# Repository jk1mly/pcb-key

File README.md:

アルプスのSKRHAAE010を使って、スイッチの状態により異なる電圧が出るようにして、A/Dして状態を読み込む基板

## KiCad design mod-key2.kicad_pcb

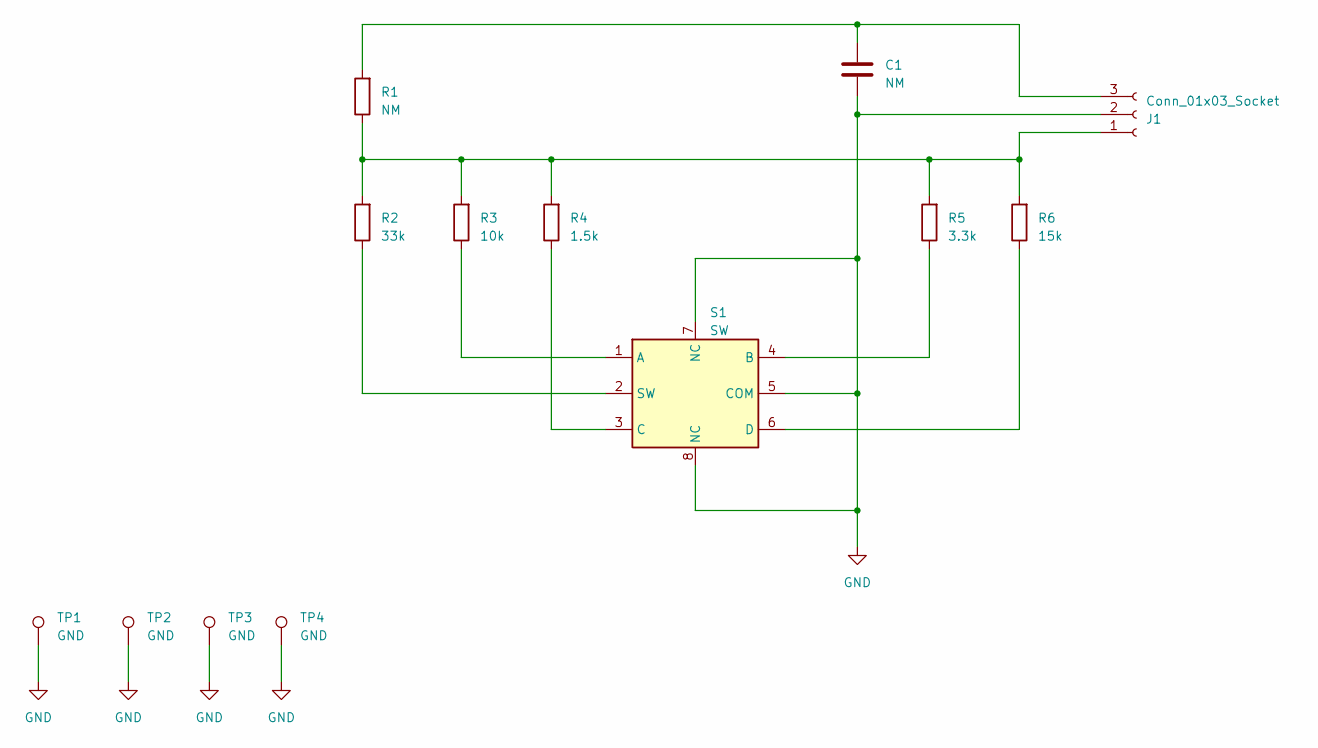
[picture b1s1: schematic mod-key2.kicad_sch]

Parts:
C1: NM; C_Disc_D3.4mm_W2.1mm_P2.50mm
J1: Conn_01x03_Socket; PinSocket_1x03_P2.54mm_Vertical
R1: NM; R_Axial_DIN0207_L6.3mm_D2.5mm_P7.62mm_Horizontal
R2: 33k; R_Axial_DIN0207_L6.3mm_D2.5mm_P7.62mm_Horizontal
R3: 10k; R_Axial_DIN0207_L6.3mm_D2.5mm_P7.62mm_Horizontal
R4: 1.5k; R_Axial_DIN0207_L6.3mm_D2.5mm_P7.62mm_Horizontal
R5: 3.3k; R_Axial_DIN0207_L6.3mm_D2.5mm_P7.62mm_Horizontal
R6: 15k; R_Axial_DIN0207_L6.3mm_D2.5mm_P7.62mm_Horizontal
S1: SW; SO-SW
TP1, TP2, TP3, TP4: GND; TestPoint_Plated_Hole_D3.0mm

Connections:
GND: C1.2, J1.2, S1.5 (COM), S1.7 (NC), S1.8 (NC), TP1.1, TP2.1, TP3.1, TP4.1
unnamed: J1.1, R1.1, R2.2, R3.2, R4.2, R5.2, R6.2
unnamed: C1.1, J1.3, R1.2
unnamed: R3.1, S1.1 (A)
unnamed: R5.1, S1.4 (B)
unnamed: R4.1, S1.3 (C)
unnamed: R6.1, S1.6 (D)
unnamed: R2.1, S1.2 (SW)

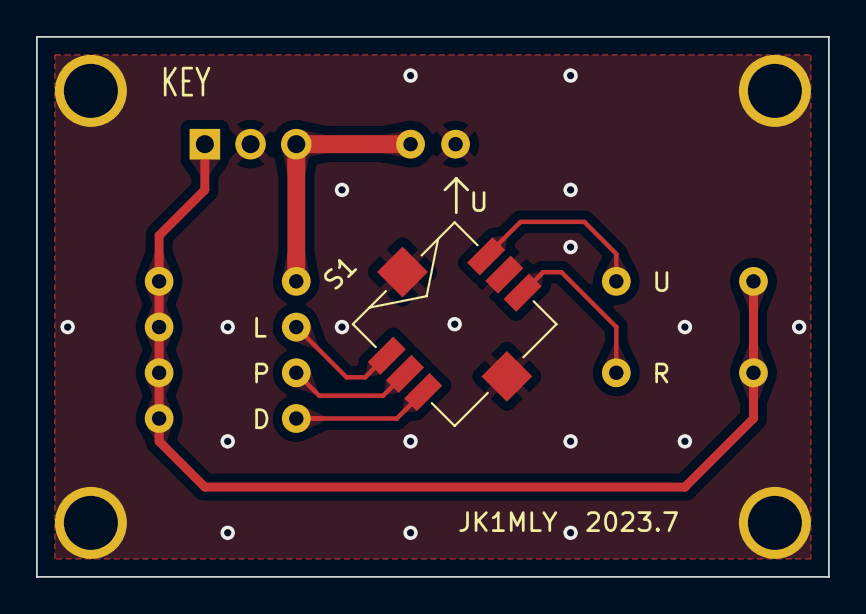
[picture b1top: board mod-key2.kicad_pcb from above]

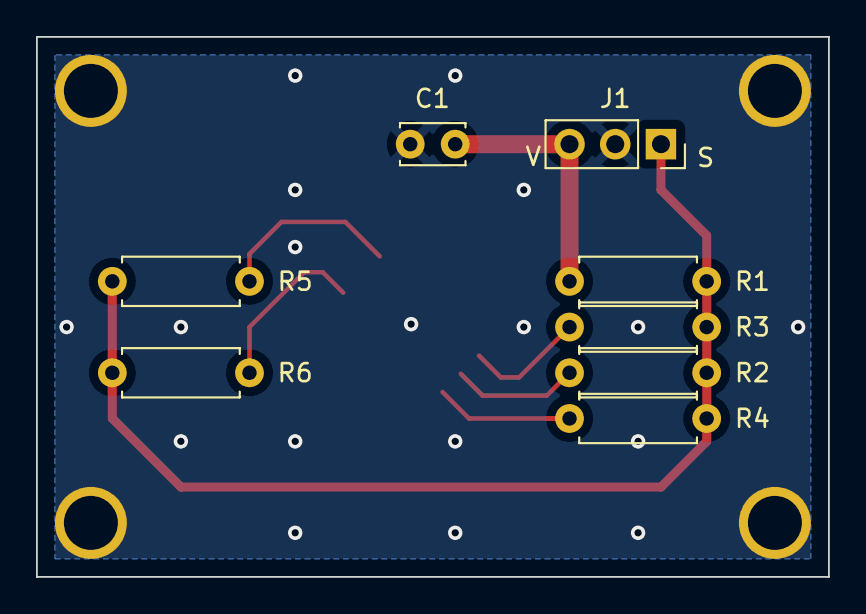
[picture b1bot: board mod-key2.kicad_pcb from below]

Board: 2 copper layers, 44.0 x 30.0 mm, 13 parts (8 on the bottom side), 8 nets.
